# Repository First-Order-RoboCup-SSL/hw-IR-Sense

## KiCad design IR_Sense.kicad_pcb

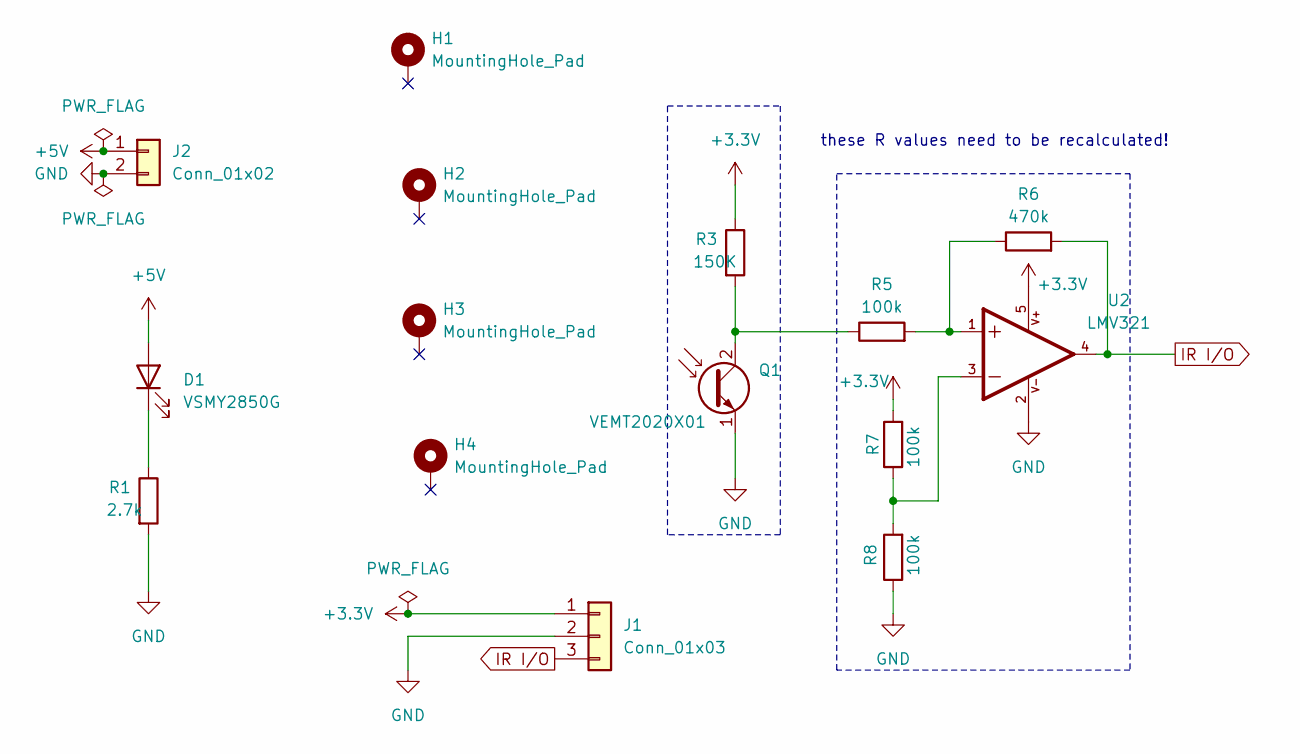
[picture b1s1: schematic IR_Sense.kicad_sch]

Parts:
D1: VSMY2850G; VSMY2850G_VEMT2020X01
H1, H2, H3, H4: MountingHole_Pad; MountingHole_2.2mm_M2_DIN965_Pad
J1: Conn_01x03; CONN-SMD_3P-P1.25_XUNPU_WAFER-MX1.25-3PCB
J2: Conn_01x02; CONN-SMD_2P-P1.25_WAFER-MX1.25-2PCB
Q1: VEMT2020X01; VSMY2850G_VEMT2020X01
R1: 2.7k; R_0603_1608Metric
R3: 150K; R_0603_1608Metric
R5, R7, R8: 100k; R_0603_1608Metric
R6: 470k; R_0603_1608Metric
U2: LMV321; SOT-23-5

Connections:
+3.3V: J1.1, R3.1, R7.2, U2.5
+5V: D1.2 (A), J2.1
GND: J1.2, J2.2, Q1.1 (E), R1.2, R8.1, U2.2
IR I/O: J1.3, R6.2, U2.4
unnamed: D1.1 (K), R1.1
unnamed: Q1.2 (C), R3.2, R5.1
unnamed: R5.2, R6.1, U2.1
unnamed: R7.1, R8.2, U2.3

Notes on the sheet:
these R values need to be recalculated!

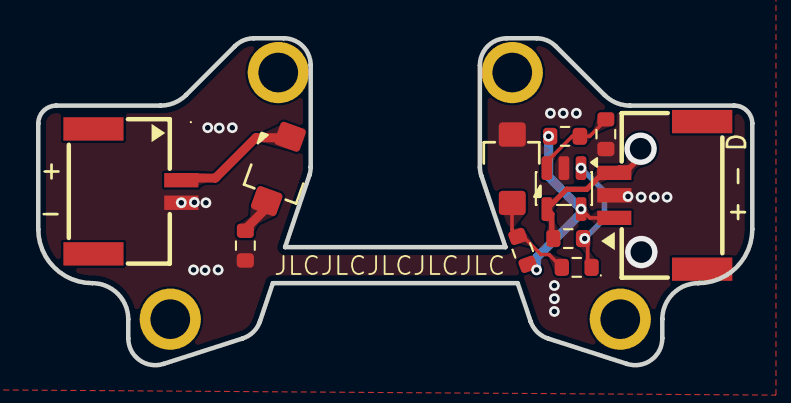
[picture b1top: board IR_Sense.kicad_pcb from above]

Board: 2 copper layers, 39.7 x 18.2 mm, 15 parts (0 on the bottom side), 8 nets.

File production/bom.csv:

Designator,Footprint,Quantity,Value,LCSC Part #
D1,VSMY2850G_VEMT2020X01,1,VSMY2850G,
J1,CONN-SMD_3P-P1.25_XUNPU_WAFER-MX1.25-3PCB,1,Conn_01x03,C3029387
J2,CONN-SMD_2P-P1.25_WAFER-MX1.25-2PCB,1,Conn_01x02,C3029386
Q1,VSMY2850G_VEMT2020X01,1,VEMT2020X01,
R1,0603,1,2.7k,
R3,0603,1,150K,
"R5, R7, R8",0603,3,100k,
R6,0603,1,470k,
U2,SOT-23-5,1,LMV321,

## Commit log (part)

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2026-05-06 new values
